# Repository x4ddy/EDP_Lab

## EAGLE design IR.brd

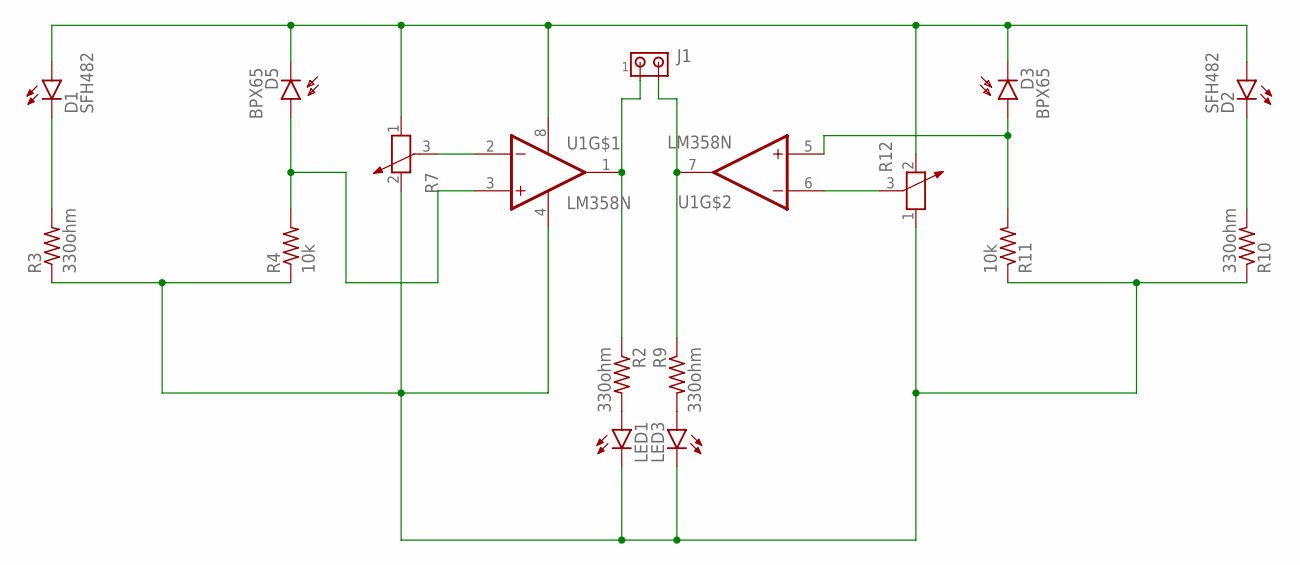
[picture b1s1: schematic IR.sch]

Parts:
D1, D2: SFH482
D3, D5: BPX65
J1: MTA02-100; 10X02MTA
LED1, LED3: LED3MM
R2, R3, R9, R10: 330ohm; 0204/5
R4, R11: 10k; 0204/5
R7, R12: POTENTIOMETER_PT-10; PT-10
U1: LM358N; DIP762W46P254L960H508Q8

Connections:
unnamed: D1.K (C), R3.2
unnamed: D5.A, R4.2, U1.3 (1IN+)
unnamed: D1.A, D2.A, D3.K (C), D5.K (C), R7.1, R12.2, U1.8 (VCC)
unnamed: LED1.K (C), LED3.K (C), R3.1, R4.1, R7.2, R10.1, R11.1, R12.1, U1.4 (GND)
unnamed: R7.3, U1.2 (1IN-)
unnamed: LED1.A, R2.2
unnamed: J1.1, R2.1, U1.1 (1OUT)
unnamed: D2.K (C), R10.2
unnamed: R12.3, U1.6 (2IN-)
unnamed: D3.A, R11.2, U1.5 (2IN+)
unnamed: J1.2, R9.1, U1.7 (2OUT)
unnamed: LED3.A, R9.2

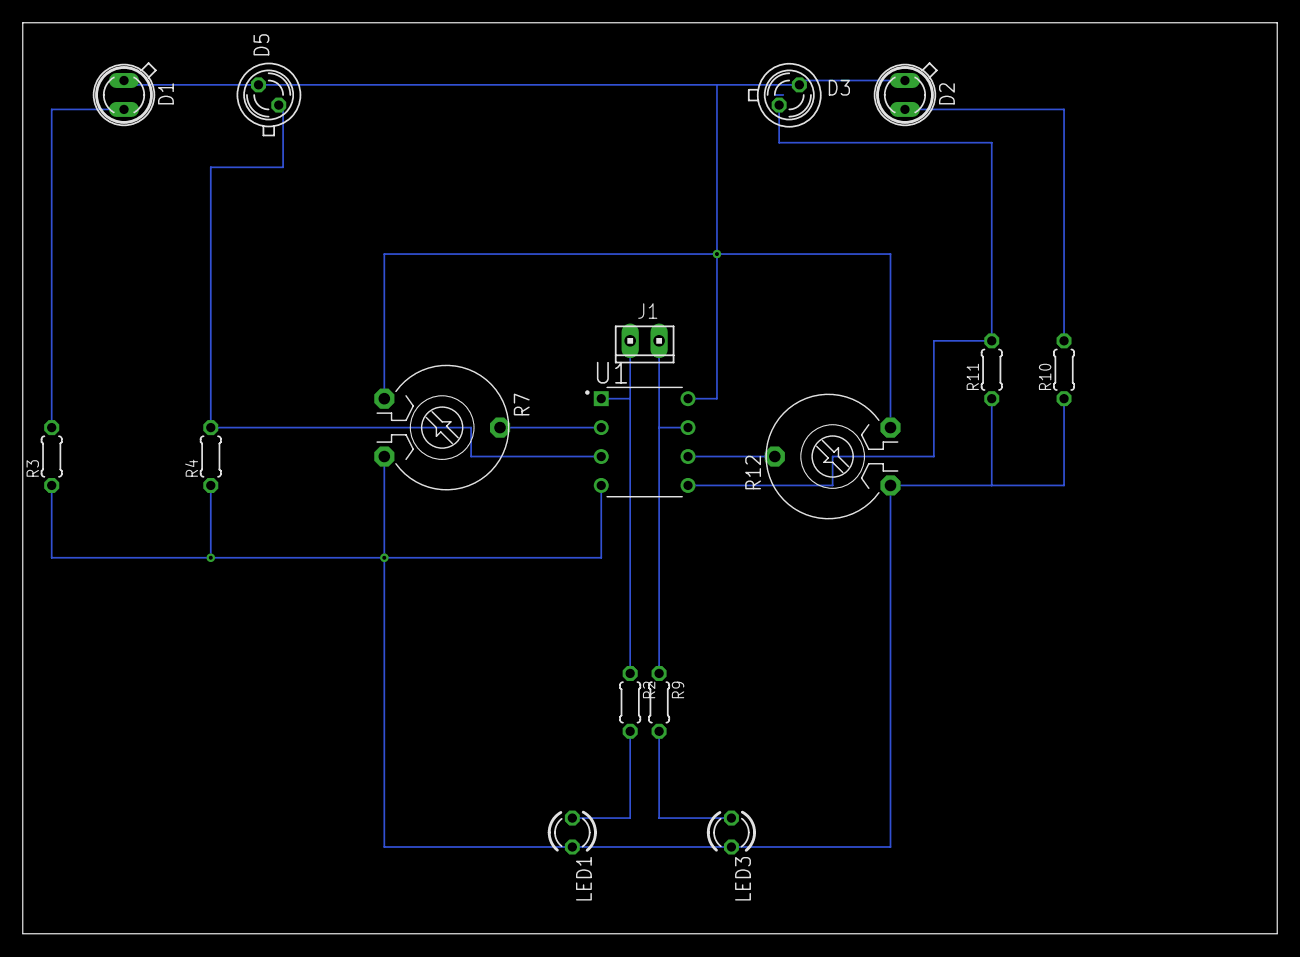
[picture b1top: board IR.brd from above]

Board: 2 copper layers, 110.2 x 80.0 mm, 16 parts (0 on the bottom side), 12 nets.

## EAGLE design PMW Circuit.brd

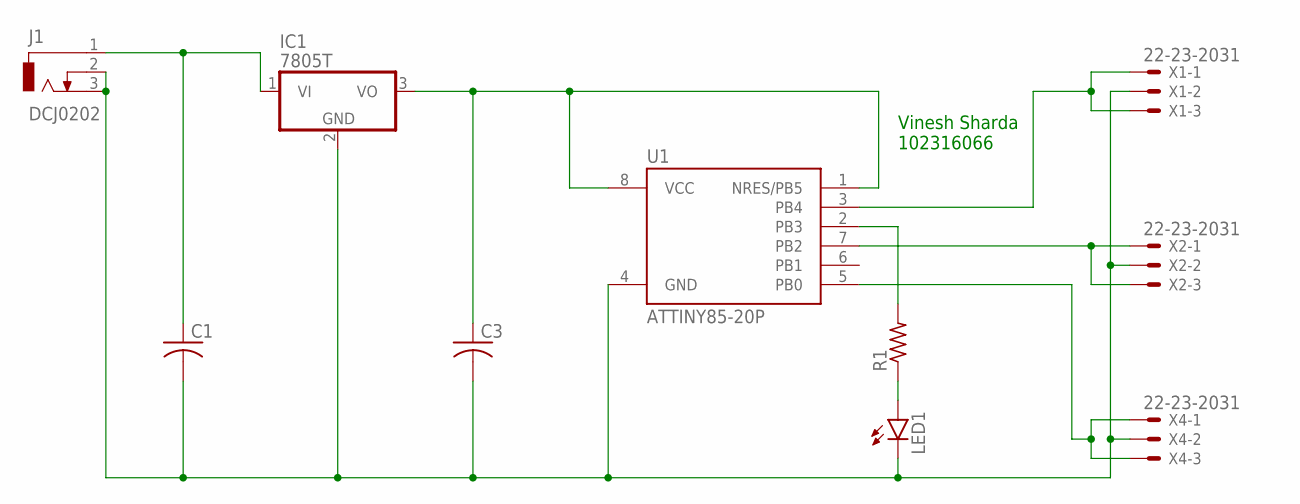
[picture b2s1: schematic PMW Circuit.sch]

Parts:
C1, C3: C-US025-024X044; C025-024X044
IC1: 7805T; TO220H
J1: DCJ0202
LED1: LED3MM
R1: R-US_0204/5; 0204/5
U1: ATTINY85-20P; PDIP08_300MIL
X1, X2, X4: 22-23-2031

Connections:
unnamed: C1.1, IC1.1 (VI), J1.1
unnamed: C3.1, IC1.3 (VO), U1.1 (NRES/PB5), U1.8 (VCC)
unnamed: C1.2, C3.2, IC1.2 (GND), J1.2, J1.3, LED1.K (C), U1.4 (GND), X1.2, X2.2, X4.2
unnamed: LED1.A, R1.1
unnamed: R1.2, U1.2 (PB3)
unnamed: U1.3 (PB4), X1.1, X1.3
unnamed: U1.7 (PB2), X2.1, X2.3
unnamed: U1.5 (PB0), X4.1, X4.3

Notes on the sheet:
Vinesh Sharda 102316066

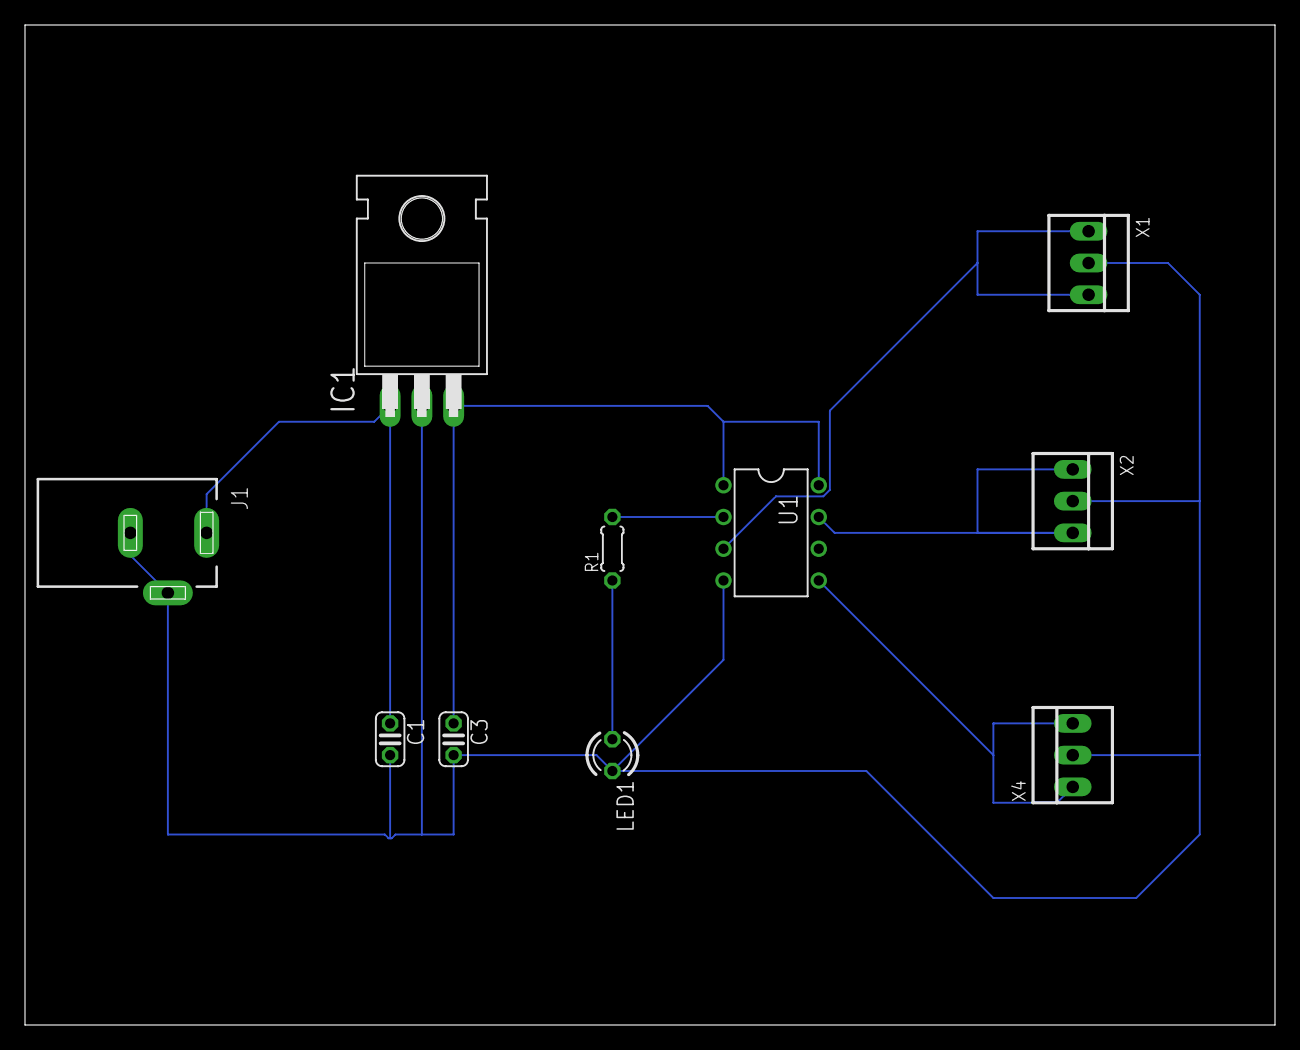
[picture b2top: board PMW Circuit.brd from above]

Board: 2 copper layers, 100.0 x 80.0 mm, 10 parts (0 on the bottom side), 8 nets.

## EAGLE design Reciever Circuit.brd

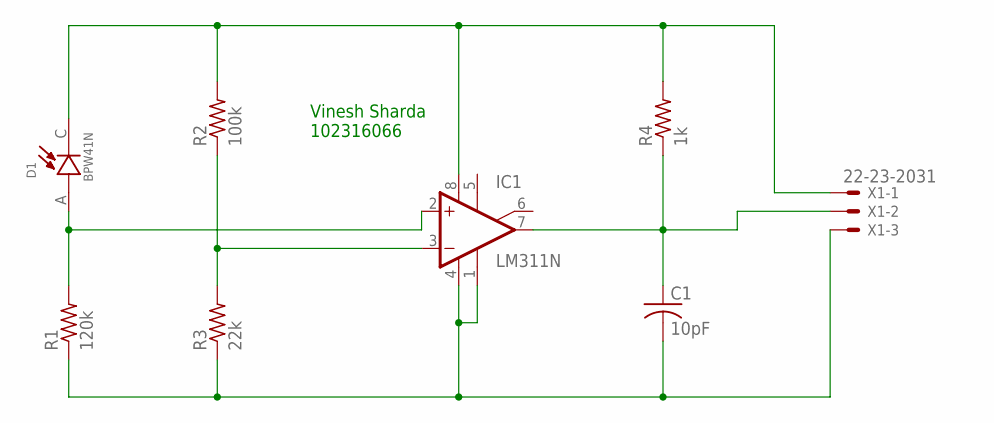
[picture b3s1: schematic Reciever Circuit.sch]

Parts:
C1: 10pF; C025-024X044
D1: BPW41N; DIO_BPW41N
IC1: LM311N; DIL08
R1: 120k; 0204/5
R2: 100k; 0204/5
R3: 22k; 0204/5
R4: 1k; 0204/5
X1: 22-23-2031

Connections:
unnamed: D1.C, IC1.8 (V+), R2.2, R4.2, X1.1
unnamed: D1.A, IC1.2 (+IN), R1.2
unnamed: IC1.3 (-IN), R2.1, R3.2
unnamed: C1.1, IC1.7 (OUT), R4.1, X1.2
unnamed: C1.2, IC1.1 (GND), IC1.4 (V-), R1.1, R3.1, X1.3

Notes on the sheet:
Vinesh Sharda 102316066

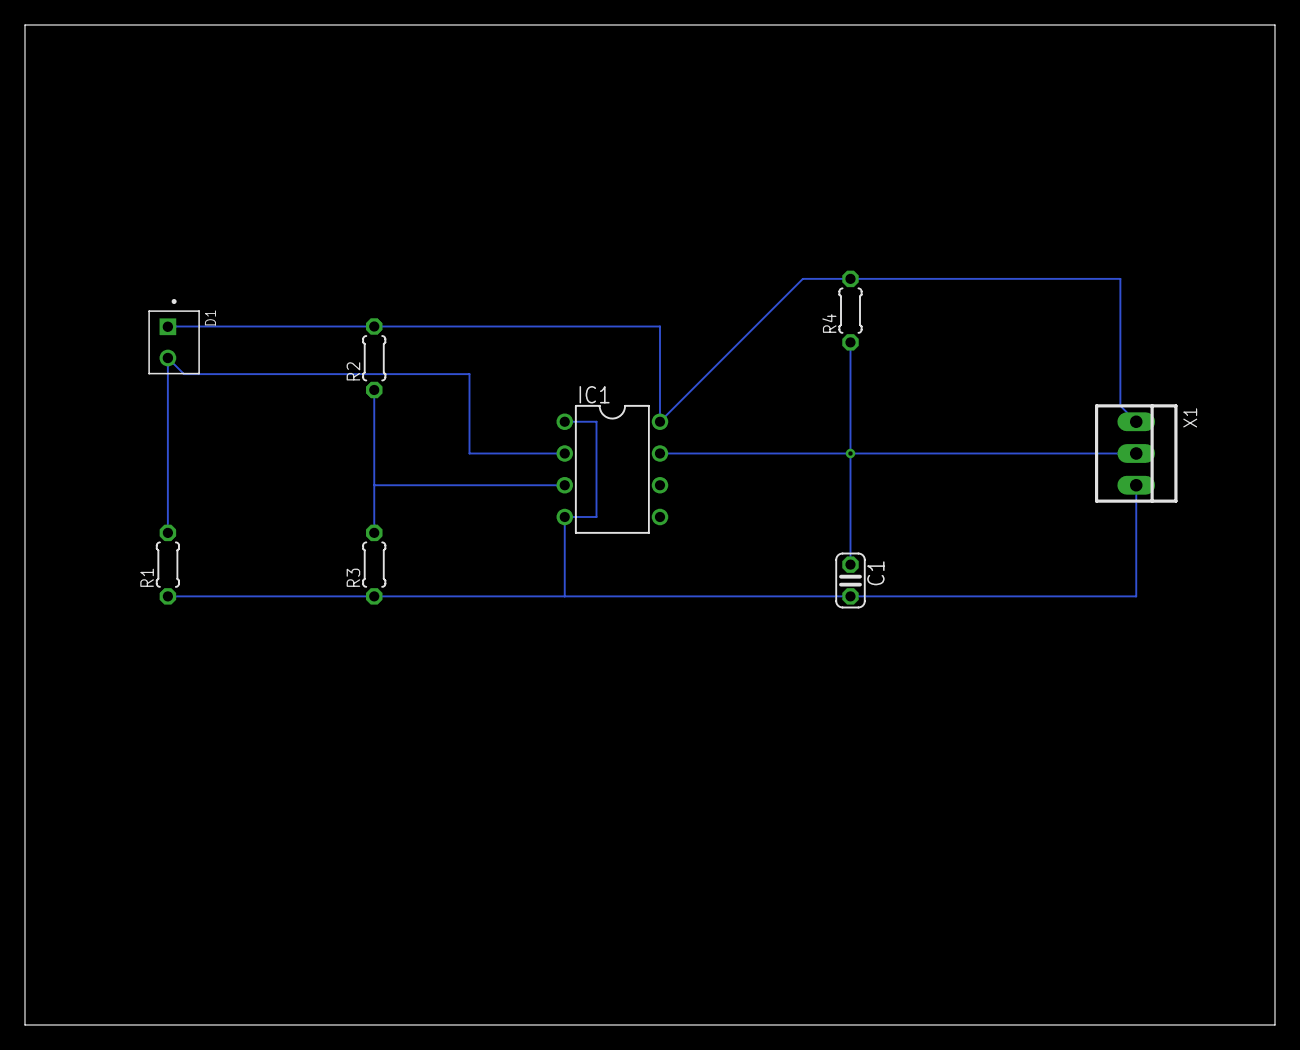
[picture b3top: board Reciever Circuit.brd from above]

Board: 2 copper layers, 100.0 x 80.0 mm, 8 parts (0 on the bottom side), 5 nets.
